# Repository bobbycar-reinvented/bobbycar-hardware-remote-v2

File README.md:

# bobbycar-hardware-remote-v2

## 3dmodels
3d models are created in Fusion 360. Only exported stl will be available here.

## firmware
This is the main firmware. It is based on other bobbycar firmware (features same gui lib for example).

## kicad
All pcb files are created in KiCad. jlcpcb exports are available, although it is recommended to check the files before ordering.

## Pictures

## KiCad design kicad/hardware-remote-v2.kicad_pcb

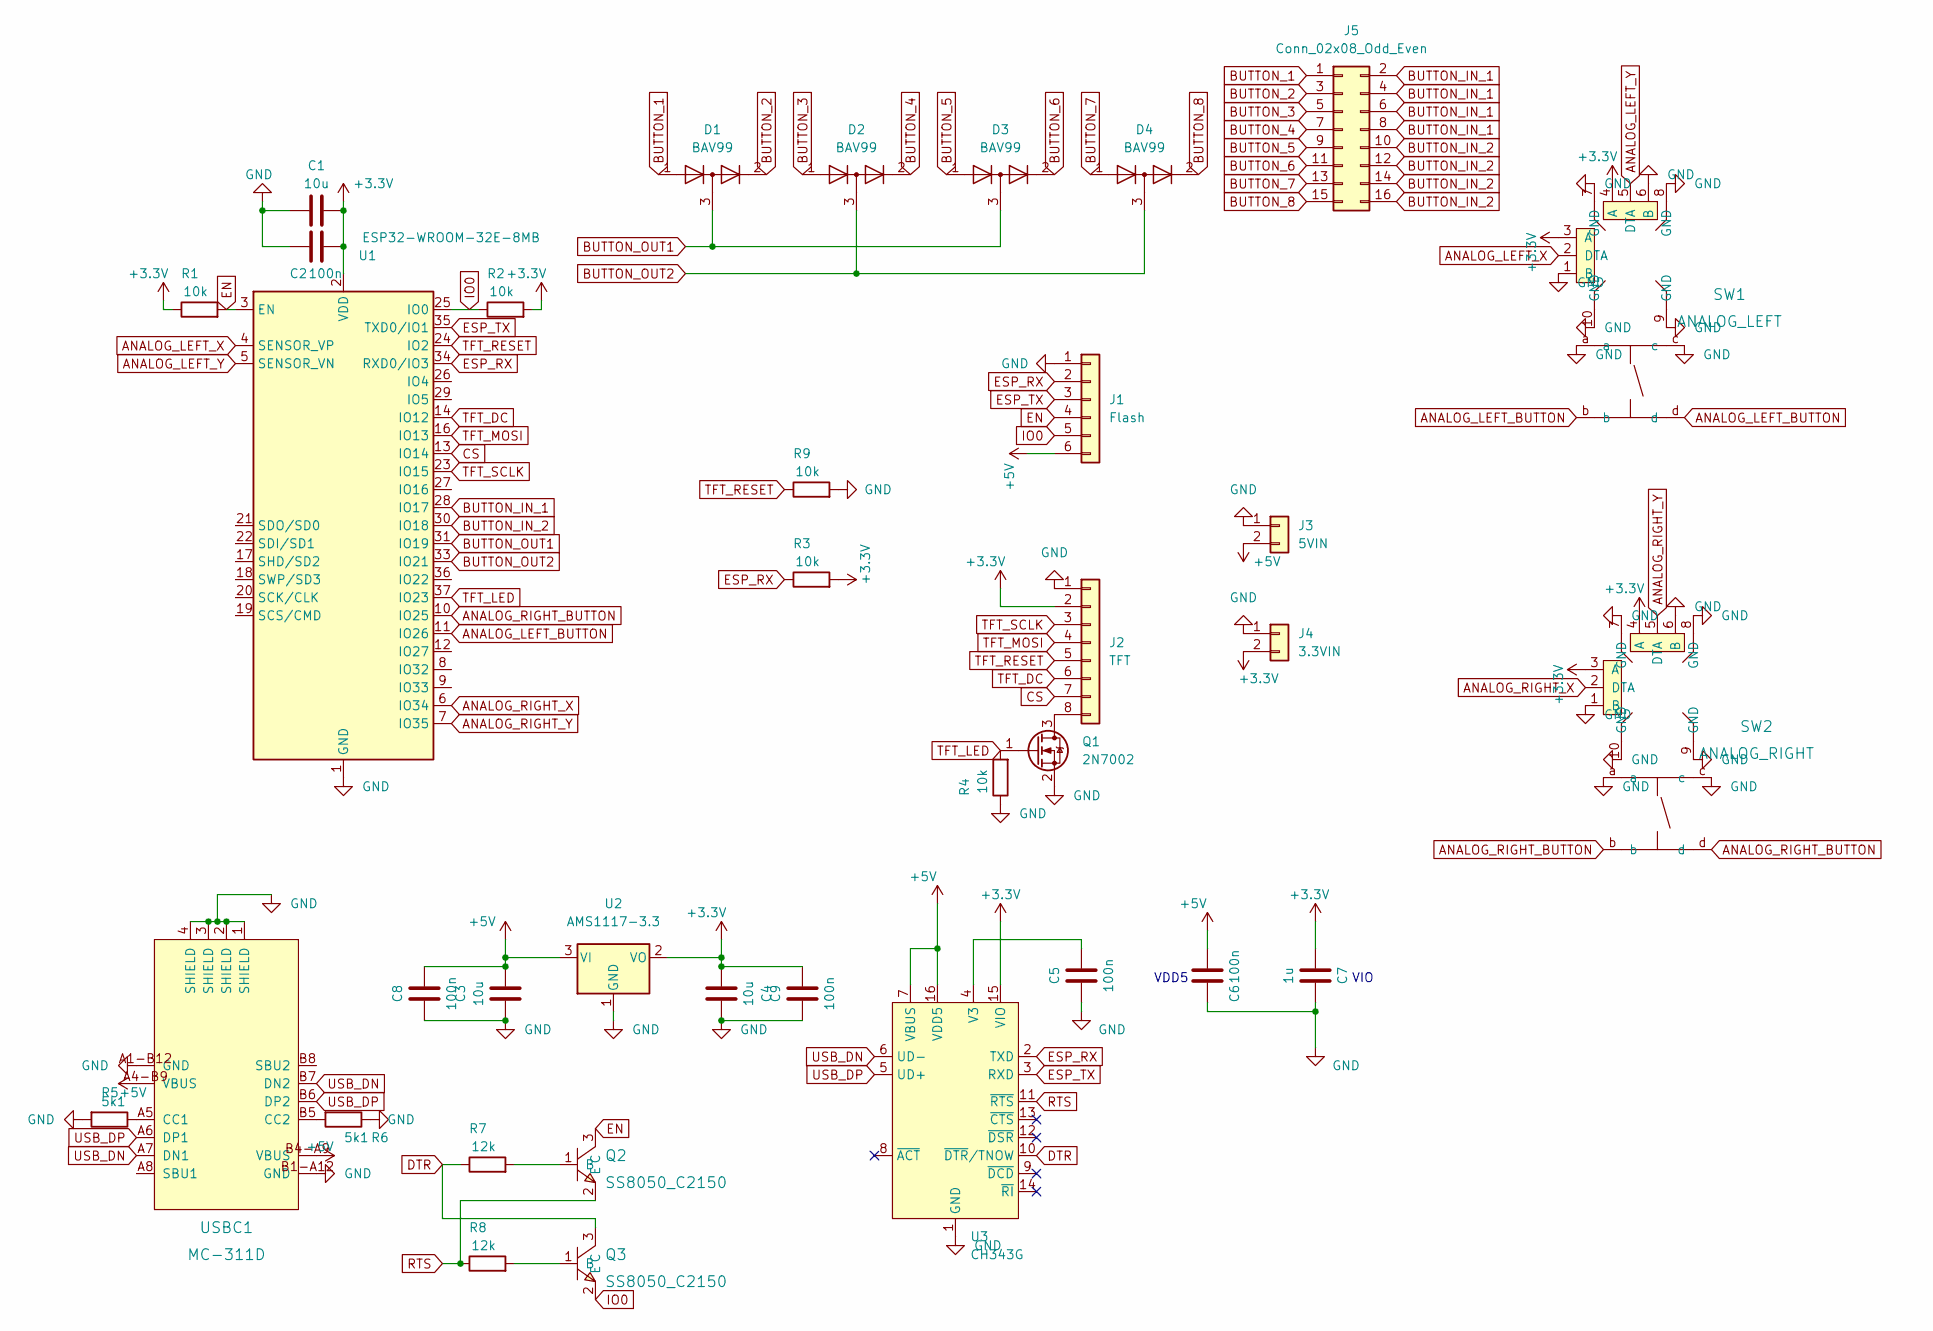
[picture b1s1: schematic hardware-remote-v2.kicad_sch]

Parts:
C1, C3, C4: 10u; C_0603_1608Metric; LCSC Part # C19702
C2, C5, C6, C8, C9: 100n; C_0603_1608Metric; LCSC Part # C14663
C7: 1u; C_0603_1608Metric; LCSC Part # C15849
D1, D2, D3, D4: BAV99; SOT-23; LCSC C2500
J1: Flash; JST_XH_B6B-XH-A_1x06_P2.50mm_Vertical
J2: TFT; PinSocket_1x08_P2.54mm_Vertical
J3: 5VIN; PinHeader_1x02_P2.54mm_Vertical
J4: 3.3VIN; PinHeader_1x02_P2.54mm_Vertical
J5: Conn_02x08_Odd_Even; PinHeader_2x08_P2.54mm_Vertical
Q1: 2N7002; SOT-23; LCSC C8545
Q2, Q3: SS8050_C2150; SOT-23-3_L2.9-W1.3-P1.90-LS2.4-BR; LCSC Part C2150
R1, R2, R3, R4, R9: 10k; R_0603_1608Metric; LCSC C25804
R5, R6: 5k1; R_0603_1608Metric; LCSC C23186
R7, R8: 12k; R_0603_1608Metric; LCSC C22790
SW1: ANALOG_LEFT; SW-TH_RKJXV122400D; LCSC Part C2687349
SW2: ANALOG_RIGHT; SW-TH_RKJXV122400D; LCSC Part C2687349
U1: ESP32-WROOM-32E-8MB; ESP32-WROOM-32; LCSC C701342
U2: AMS1117-3.3; SOT-223-3_TabPin2; LCSC C6186
U3: CH343G; SOIC-16_3.9x9.9mm_P1.27mm; LCSC C2844153
USBC1: MC-311D; USB-C-SMD_MC-311D; LCSC Part C136423

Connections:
+3V3: C1.2, C2.2, C4.1, C7.2, C9.2, J2.2, J4.2, R1.1, R2.2, R3.2, SW1.3 (A), SW1.4 (A), SW2.3 (A), SW2.4 (A), U1.2 (VDD), U2.2 (VO), U3.15 (VIO)
+5V: C3.2, C6.2, C8.2, J1.6, J3.2, U2.3 (VI), U3.7 (VBUS), U3.16 (VDD5), USBC1.A4-B9 (VBUS), USBC1.B4-A9 (VBUS); also elsewhere on the board
ANALOG_LEFT_BUTTON: SW1.b, SW1.d, U1.11 (IO26)
ANALOG_LEFT_X: SW1.2 (DTA), U1.4 (SENSOR_VP)
ANALOG_LEFT_Y: SW1.5 (DTA), U1.5 (SENSOR_VN)
ANALOG_RIGHT_BUTTON: SW2.b, SW2.d, U1.10 (IO25)
ANALOG_RIGHT_X: SW2.2 (DTA), U1.6 (IO34)
ANALOG_RIGHT_Y: SW2.5 (DTA), U1.7 (IO35)
BUTTON_1: D1.1 (K), J5.1
BUTTON_2: D1.2 (A), J5.3
BUTTON_3: D2.1 (K), J5.5
BUTTON_4: D2.2 (A), J5.7
BUTTON_5: D3.1 (K), J5.9
BUTTON_6: D3.2 (A), J5.11
BUTTON_7: D4.1 (K), J5.13
BUTTON_8: D4.2 (A), J5.15
BUTTON_IN_1: J5.2, J5.4, J5.6, J5.8, U1.28 (IO17)
BUTTON_IN_2: J5.10, J5.12, J5.14, J5.16, U1.30 (IO18)
BUTTON_OUT1: D1.3 (K), D3.3 (K), U1.31 (IO19)
BUTTON_OUT2: D2.3 (K), D4.3 (K), U1.33 (IO21)
CS: J2.7, U1.13 (IO14)
DTR: Q3.3 (C), R7.1, U3.10 (~DTR/TNOW)
EN: J1.4, Q2.3 (C), R1.2, U1.3 (EN); also elsewhere on the board
ESP_RX: J1.2, R3.1, U1.34 (RXD0/IO3), U3.2 (TXD); also elsewhere on the board
ESP_TX: J1.3, U1.35 (TXD0/IO1), U3.3 (RXD); also elsewhere on the board
GND: C1.1, C2.1, C3.1, C4.2, C5.1, C6.1, C7.1, C8.1, C9.1, J1.1, J2.1, J3.1, J4.1, Q1.2 (S), R4.1, R5.2, R6.1, R9.2, SW1.1 (B), SW1.6 (B), SW1.7 (GND), SW1.8 (GND), SW1.9 (GND), SW1.10 (GND), SW1.a, SW1.c, SW2.1 (B), SW2.6 (B), SW2.7 (GND), SW2.8 (GND), SW2.9 (GND), SW2.10 (GND), SW2.a, SW2.c, U1.1 (GND), U1.15 (GND), U1.38 (GND), U1.39 (GND), U2.1 (GND), U3.1 (GND), USBC1.1 (SHIELD), USBC1.2 (SHIELD), USBC1.3 (SHIELD), USBC1.4 (SHIELD), USBC1.A1-B12 (GND), USBC1.B1-A12 (GND); also elsewhere on the board
IO0: J1.5, Q3.2 (E), R2.1, U1.25 (IO0); also elsewhere on the board
unnamed: C5.2, U3.4 (V3)
unnamed: J2.8, Q1.3 (D)
unnamed: Q2.1 (B), R7.2
unnamed: Q3.1 (B), R8.2
unnamed: R5.1, USBC1.A5 (CC1)
unnamed: R6.2, USBC1.B5 (CC2)
RTS: Q2.2 (E), R8.1, U3.11 (~RTS)
TFT_DC: J2.6, U1.14 (IO12)
TFT_LED: Q1.1 (G), R4.2, U1.37 (IO23)
TFT_MOSI: J2.4, U1.16 (IO13)
TFT_RESET: J2.5, R9.1, U1.24 (IO2)
TFT_SCLK: J2.3, U1.23 (IO15)
USB_DN: U3.6 (UD-), USBC1.A7 (DN1), USBC1.B7 (DN2)
USB_DP: U3.5 (UD+), USBC1.A6 (DP1), USBC1.B6 (DP2)

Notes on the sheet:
VDD5
VIO

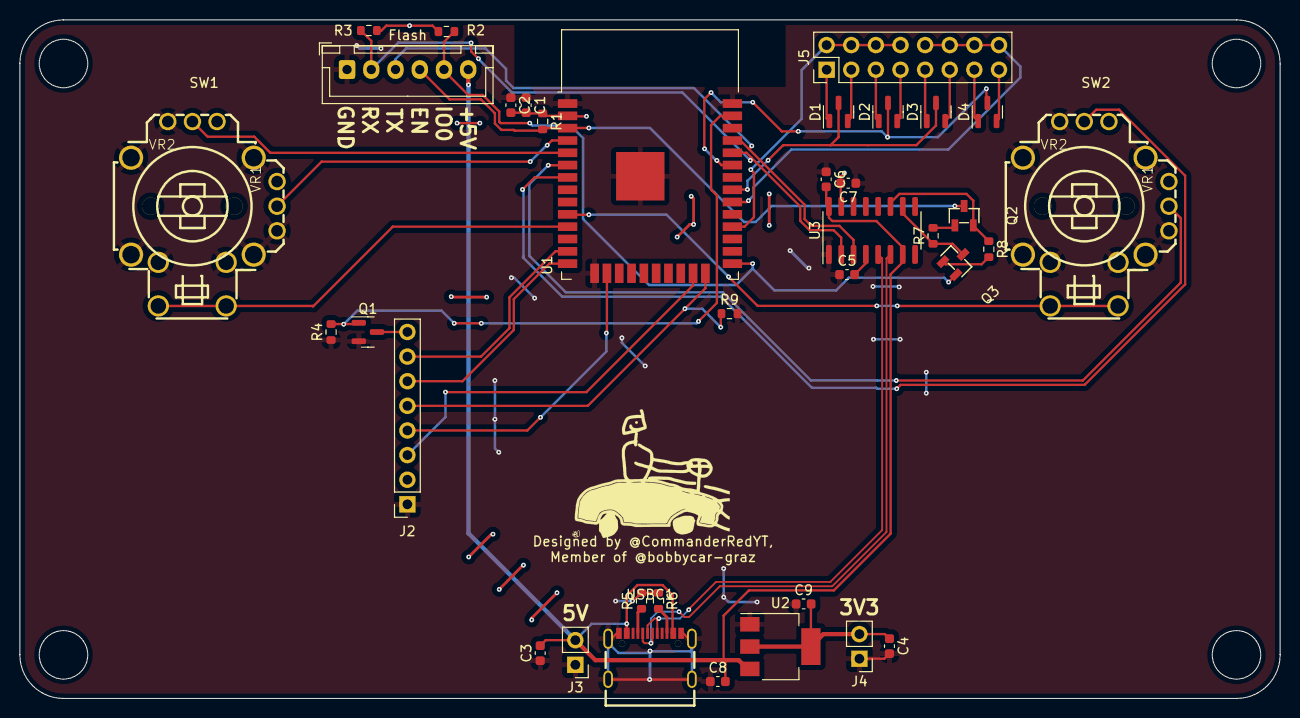
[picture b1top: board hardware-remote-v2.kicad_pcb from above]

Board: 2 copper layers, 130.0 x 70.0 mm, 36 parts (0 on the bottom side), 41 nets.

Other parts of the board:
Flash: Flash; JST_XH_B6B-XH-A_1x06_P2.50mm_Vertical

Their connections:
+5V: Flash.6; also elsewhere on the board
EN: Flash.4; also elsewhere on the board
ESP_RX: Flash.2; also elsewhere on the board
ESP_TX: Flash.3; also elsewhere on the board
GND: Flash.1; also elsewhere on the board
IO0: Flash.5; also elsewhere on the board

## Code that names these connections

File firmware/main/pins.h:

#pragma once

namespace analog_sticks::pins {
constexpr auto left_x = PIN_ANALOG_LEFT_X;
constexpr auto left_y = PIN_ANALOG_LEFT_Y;
constexpr auto left_btn = PIN_ANALOG_LEFT_BTN;

constexpr auto right_x = PIN_ANALOG_RIGHT_X;
constexpr auto right_y = PIN_ANALOG_RIGHT_Y;
constexpr auto right_btn = PIN_ANALOG_RIGHT_BTN;
} // namespace analog_sticks::pins

namespace buttons::pins {
constexpr auto OUT1 = PIN_BTN_OUT1;
constexpr auto OUT2 = PIN_BTN_OUT2;
constexpr auto IN1 = PIN_BTN_IN1;
constexpr auto IN2 = PIN_BTN_IN2;
} // namespace buttons::pins

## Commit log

2022-05-16 Added PCB
2022-05-16 Updated jlc
2022-05-16 Updated usb, still needs someone to put flasher on there
2022-05-19 PCB Version Beta 0.1
2022-05-19 Fixed DRC
2022-05-19 Exported new production files
2022-05-19 Actually use usb c that they can solder
2022-05-20 Should be final design, but jlcpcbs rotation is weird
2022-05-20 Production files
2022-06-28 Fixed submodules
2022-07-06 Added 3d models
2022-07-06 Updated / fixed pcb
2022-07-06 Added bobbyicon sources
2022-07-06 Initial submodules etc
2022-07-06 Updated remote paths
2022-07-06 Added more files
2022-07-06 Added bobbyicons
2022-07-06 Added tools
2022-07-06 Fixed gitignore
2022-07-06 Fixed cmakelists
2022-07-06 Updated submodules
2022-07-06 Everything compiles and runs
2022-07-06 Changed port
2022-07-06 Added esp-protocols
2022-07-06 Basic files for chip config
2022-07-06 Added basic program structure
2022-07-06 Implemented basic ui, analog sticks and more
2022-07-06 Implemented basic UI
2022-07-06 Added loading screen
2022-07-06 Added buttons
2022-07-06 Changed some nimble settings
2022-07-06 It drives now.
2022-07-06 Implemented reconnect etc
2022-09-13 Added readme
2022-09-13 Added gitignore
2022-09-13 Added ble gamepad support
2022-09-13 Added button logging
2022-09-13 Control backlight for gamecontroller
2022-09-14 Updated submodule
2026-04-06 Try to update everything, wip, help
2026-04-06 Yay it works
